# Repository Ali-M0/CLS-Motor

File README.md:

# CLS-Motor: A compact solution for stepper motors
<br>
<br>

<br>
<br>

<br>
Why not improve the capabilities of an already abundant and capable motor.
<br>

## Key Features

<br>
- Real-time closed-loop correction using MT6816 magnetic encoder
<br>
- **Communication via CAN bus:** By utilizing a CAN bus communication protocol, you inherently gain several benefits to your system, the main benefits being a robust communication protocol that was made with low EMI in mind, along with a more accurate system that decreases the amount of wires needed and scalability with other CLS-Motor systems.
<br>
- **6-layer custom PCB:** Designed in KiCad for signal integrity and thermal performance
<br>
- **Onboard STM32F103CBT6:** Handles encoder data and CAN communication
<br>
- Power regulation via LP2992AIM5-3.3 linear regulator
<br>
- Fully custom C++ to come (CLion environment)

<br>
<br>

## Motivation
In robotic systems—especially robotic arms—accuracy and reliability are critical. While working on my own robotic arm project, I noticed that traditional open-loop stepper motors often missed steps under load, compromising precision.
<br>
<br>
To solve this, I developed the Closed-Loop Stepper (CLS) Motor system—an integrated hardware/software solution that enables real-time position correction through encoder feedback and control logic.
<br>
<br>
<br>

FUTURE PLANS
<br>

># Correction Software for CLS Motor
>
><br>
><br>
>
> Explanation about my STM32 programming coming soon with demo and visuals.
> <br>
> Implementation of a diagnostic serial output to aid in tuning and debugging the control loop in real-world conditions.
> <br>
> Custom C++ software using a PID control system and FOC controller to detect missing steps, sending signals to then correct the lost steps
> <br>
>

<br>
<br>
<br>
<br>

## Technical Specifications/Overview

<br>

A closed-loop control system designed to stack with stepper motors and provide real-time feedback using a magnetic encoder. It detects missed steps and corrects them using an onboard STM32 microcontroller while also supplying your communication line through the CAN bus ports to your main microcontroller.

  <br>

In the field of robotics, precision and reliability in motor control are essential. During the development of my robotic arm project, I identified the limitations of traditional open-loop stepper systems, particularly their inability to self-correct under load. To address this, I designed and implemented a closed-loop stepper motor driver, combining custom hardware and software to enable real-time position correction.

  <br>

This project involved designing a 6-layer PCB in KiCad, optimized for signal integrity and thermal performance. At its core is an STM32F103CBT6 microcontroller, chosen for its surprisingly high processing speed, rich I/O capabilities, and the fact that its only main purpose is to power the encoder and CAN transceiver, along with any other I/O necessary within the board. I integrated an MT6816 magnetic rotary encoder on the rear shaft of a NEMA 17 stepper motor to provide high-resolution feedback, enabling the system to compare target and actual positions. Through custom correction software written in C++ using CLion, the CLS system adjusts its actuation based on the previous and current step resolution. The CLS motor system also integrates an SN65HVD232 CAN transceiver that, on the surface, enables communication between the main CAN controller located on the main MCU, that being a Teensy 4.1, and the CAN bus ports, supplying my system with its communication signal.

  <br>

You also may be wondering how my system is powered. That's done through a cascade power system that cascades through a daisy chain design and supplies power to all motors using the CLS motor system, being ultimately powered by a +5V power supply that's soldered to the PCB's positive and negative solder pads added to the top and bottom of the board. The system regulates the +5V power supply to a +3.3V output rail through an LP2992AIM5-3.3 linear regulator, and this then provides power to all the necessary components within my system.

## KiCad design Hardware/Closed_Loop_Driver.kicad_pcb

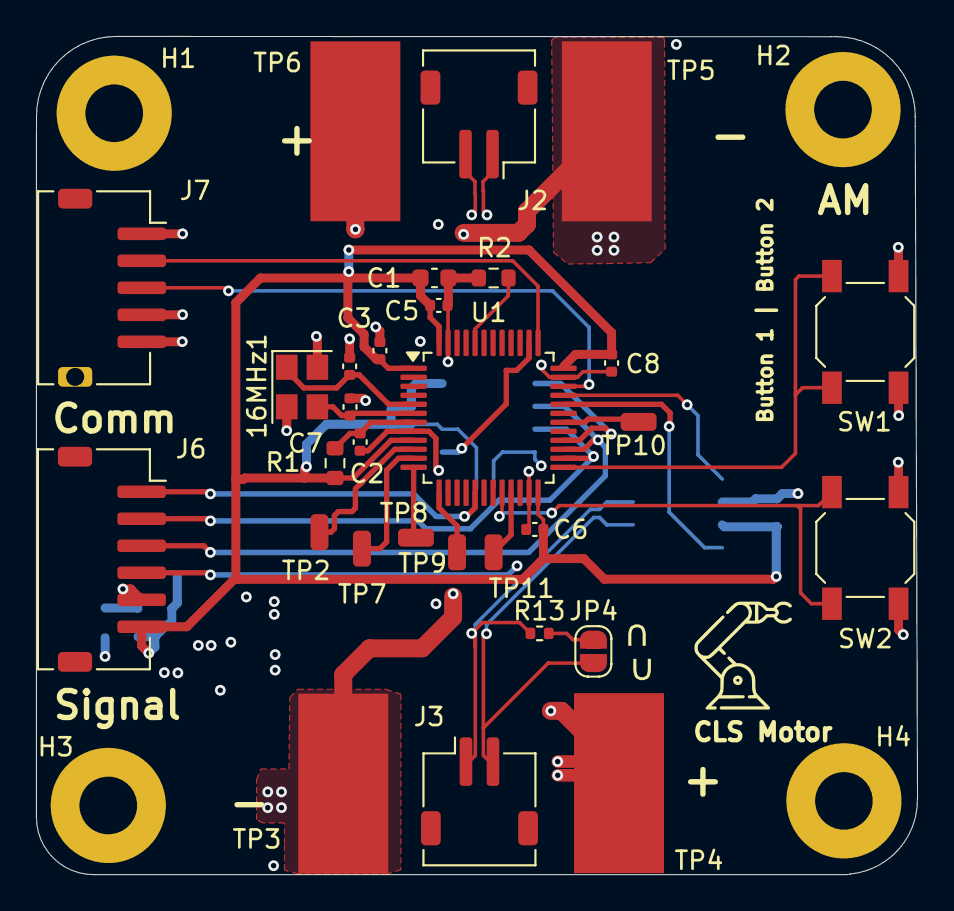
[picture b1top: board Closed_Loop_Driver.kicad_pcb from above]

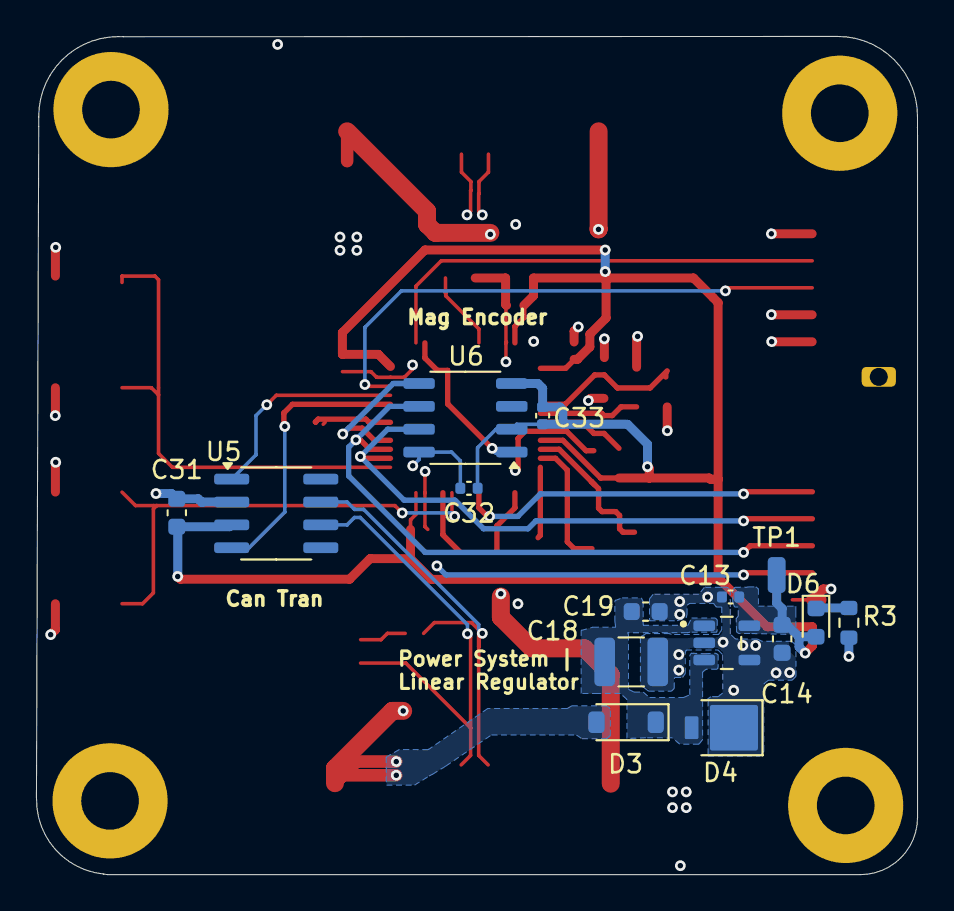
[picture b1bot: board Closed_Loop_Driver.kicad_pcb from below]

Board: 6 copper layers, 48.9 x 46.6 mm, 49 parts (15 on the bottom side), 29 nets.

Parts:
16MHz1: Crystal_GND24; Crystal_SMD_3225-4Pin_3.2x2.5mm
C1, C14, C19, C31: 10µF; C_0603_1608Metric
C2, C3, C5, C6, C8, C32: 100nF; C_0402_1005Metric
C4, C7: 10pF; C_0402_1005Metric
C13: 0.1µF; C_0402_1005Metric
C18: 100µF; C_1210_3225Metric
C33: 1µF; C_0402_1005Metric
D3: D_Filled; D_SOD-123
D4: D_TVS; D_SMP_DO-220AA
D6: RED; D_0603_1608Metric
H1, H2, H3, H4: MountingHole_Pad; MountingHole_3.2mm_M3_Pad
J2, J3: Conn_01x02; JST_ZH_S2B-ZR-SM4A-TF_1x02-1MP_P1.50mm_Horizontal
J6: Conn_01x06; JST_ZH_S6B-ZR-SM4A-TF_1x06-1MP_P1.50mm_Horizontal
J7: Conn_01x05; JST_ZH_S5B-ZR-SM4A-TF_1x05-1MP_P1.50mm_Horizontal
JP4: SolderJumper_2_Open; SolderJumper-2_P1.3mm_Open_RoundedPad1.0x1.5mm
R1, R2: 10k; R_0603_1608Metric
R3: 1.8K; R_0603_1608Metric
R13: 120R; R_0402_1005Metric
SW1, SW2: SW_Push; SW_SPST_SKQG_WithStem
TP1, TP2, TP7, TP8, TP9, TP10, TP11: TestPoint; SolderWirePad_1x01_SMD_1x2mm
TP3, TP4, TP5, TP6: TestPoint; SolderWirePad_1x01_SMD_5x10mm
U1: STM32F103CBTx; LQFP-48_7x7mm_P0.5mm
U3: LP2992AIM5-3.3; SOT95P280X145-5N
U5: SN65HVD232; SOIC-8_3.9x4.9mm_P1.27mm
U6: MT6816CT; SO-8_3.9x4.9mm_P1.27mm

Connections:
+3.3V: C1.1, C3.1, C5.1, C6.1, C8.1, C13.1, C14.2, C31.1, C32.1, C33.1, C33.2, D6.2 (A), J6.6, R1.2, TP1.1, U1.1 (VBAT), U1.9 (VDDA), U1.24 (VDD), U1.36 (VDD), U1.48 (VDD), U3.5 (VOUT), U5.3 (VCC), U6.2 (HVPP), U6.4 (VDD)
/Connection Ports/CAN_N: J2.1, J3.2, JP4.2 (B), U5.6 (CANL)
/Connection Ports/CAN_P: J2.2, J3.1, R13.1, U5.7 (CANH)
/DIR: TP8.1, U1.12 (PA2)
/ENN: TP7.1, U1.11 (PA1)
/INDEX: TP2.1, U1.10 (PA0)
/IN_PWN: TP11.1, U1.21 (PB10)
/MCU_BOOT0: R2.2, U1.44 (BOOT0)
/MCU_NRST: C2.1, R1.1, U1.7 (NRST)
/MCU_OSC_IN: 16MHz1.1, C4.1, U1.5 (PD0)
/MCU_OSC_OUT: 16MHz1.3, C7.1, U1.6 (PD1)
/PDN_UART: TP10.1, U1.30 (PA9)
/Power Supply/PWR_LED_K: D6.1 (K), R3.2
/STEP: TP9.1, U1.13 (PA3)
BTN_1: SW1.2, U1.25 (PB12)
BTN_2: SW2.2, U1.20 (PB2)
CAN_RX: U1.32 (PA11), U5.4 (R)
CAN_TX: U1.33 (PA12), U5.1 (D)
GND: 16MHz1.2, 16MHz1.4, C1.2, C2.2, C3.2, C4.2, C5.2, C6.2, C7.2, C8.2, C13.2, C14.1, C18.2, C19.2, C31.2, C32.2, D4.1 (A1), H1.1, H2.1, H3.1, H4.1, J6.5, J7.1, J7.4, J7.5, R2.1, R3.1, SW1.1, SW2.1, TP3.1, TP5.1, U1.8 (VSSA), U1.23 (VSS), U1.35 (VSS), U1.47 (VSS), U3.2 (GND), U3.4 (BYPASS), U5.2 (GND), U6.8 (GND)
MT6816_AUX_CS: J6.1, U1.17 (PA7)
MT6816_CS: U1.38 (PA15), U6.1 (~CS)
unnamed: JP4.1 (A), R13.2
SPI2_MISO: J6.3, U1.27 (PB14), U6.6 (B/V)
SPI2_MOSI: J6.4, U1.28 (PB15), U6.5 (A/U)
SPI2_SCK: J6.2, U1.26 (PB13), U6.7 (Z/W)
SWCLK: J7.2, U1.37 (PA14)
SWDIO: J7.3, U1.34 (PA13)
VCC: C18.1, C19.1, D3.1 (K), D4.2 (A2), U3.1 (VIN), U3.3 (ON/~OFF)
VCC_IN_5V: D3.2 (A), TP4.1, TP6.1

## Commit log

2025-07-01 Organized into hardware files
2026-03-29 Create Software

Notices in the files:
README.md:
License: MIT
